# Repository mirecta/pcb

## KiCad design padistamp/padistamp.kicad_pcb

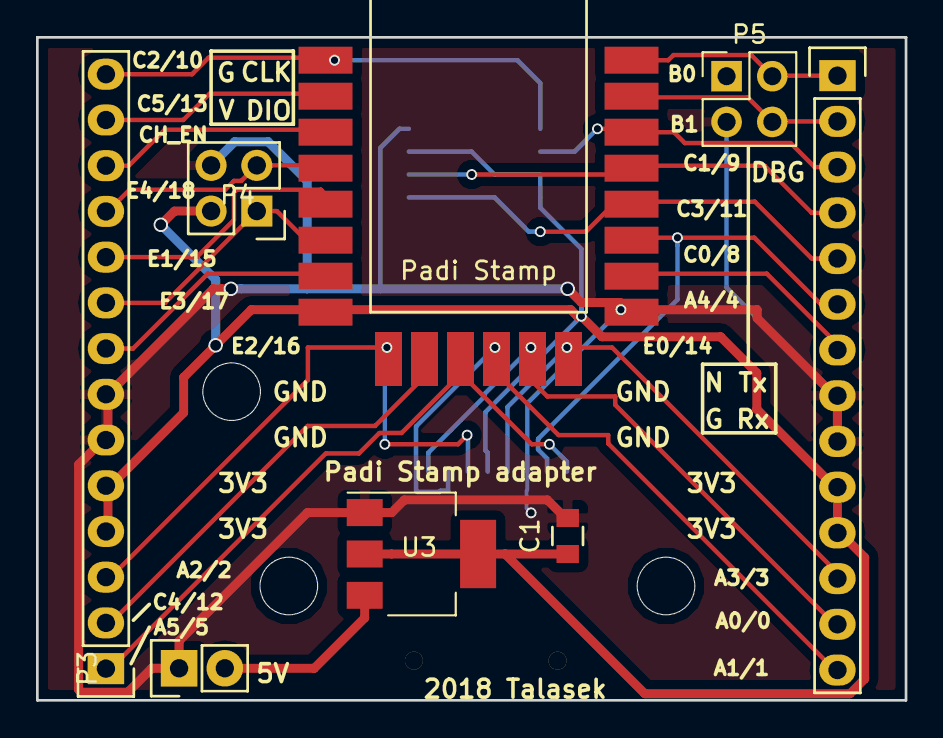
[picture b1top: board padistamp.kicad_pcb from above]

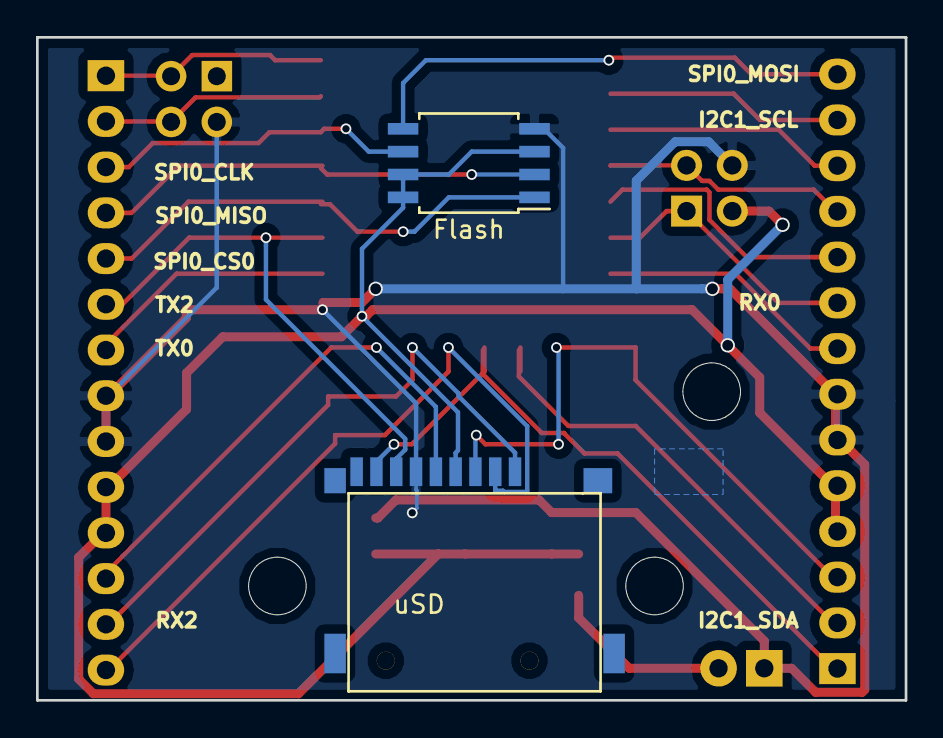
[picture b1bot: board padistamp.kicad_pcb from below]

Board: 2 copper layers, 48.3 x 36.8 mm, 10 parts (2 on the bottom side), 23 nets.

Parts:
C1: 0.1u; C_0805
Flash: 25LC_EEPROM; SOIJ-8_5.3x5.3mm_Pitch1.27mm
P1, P2: CONN_01X14; Pin_Header_Straight_1x14
P3: 5V; Pin_Header_Straight_1x02
P4: SWD; Pin_Header_Straight_2x02
P5: Conn_02x02_Odd_Even; Pin_Header_Straight_2x02_Pitch2.54mm
Padi Stamp: padi_stamp
U3: TLV1117; SOT-223
uSD: uSD

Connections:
unnamed: C1.1, Flash.3, Flash.7, Flash.8, P1.4, P1.5, P2.10, P2.11, P4.2, Padi Stamp.8, U3.2, U3.4, uSD.4
unnamed: C1.2, Flash.4, P1.6, P1.7, P2.8, P2.9, P3.1, P4.4, P5.3, Padi Stamp.15, U3.1, uSD.6
unnamed: P1.1, Padi Stamp.11, uSD.8
unnamed: P1.2, Padi Stamp.10
unnamed: P1.3, Padi Stamp.9, uSD.3
unnamed: P1.8, Padi Stamp.7
unnamed: P1.9, P4.1, Padi Stamp.6
unnamed: P1.10, Padi Stamp.5
unnamed: P1.11, P4.3, Padi Stamp.4
unnamed: P1.12, Padi Stamp.3
unnamed: P1.13, Padi Stamp.2
unnamed: Flash.5, P1.14, Padi Stamp.1
unnamed: P2.1, P5.2, Padi Stamp.22
unnamed: P2.2, P5.4, Padi Stamp.21
unnamed: Flash.6, P2.3, Padi Stamp.20
unnamed: Flash.2, P2.4, Padi Stamp.19
unnamed: Flash.1, P2.5, Padi Stamp.18
unnamed: P2.6, Padi Stamp.17, uSD.7
unnamed: P2.7, Padi Stamp.16
unnamed: P2.12, Padi Stamp.14, uSD.5
unnamed: P2.13, Padi Stamp.13, uSD.1
unnamed: P2.14, Padi Stamp.12, uSD.2
unnamed: P3.2, U3.3

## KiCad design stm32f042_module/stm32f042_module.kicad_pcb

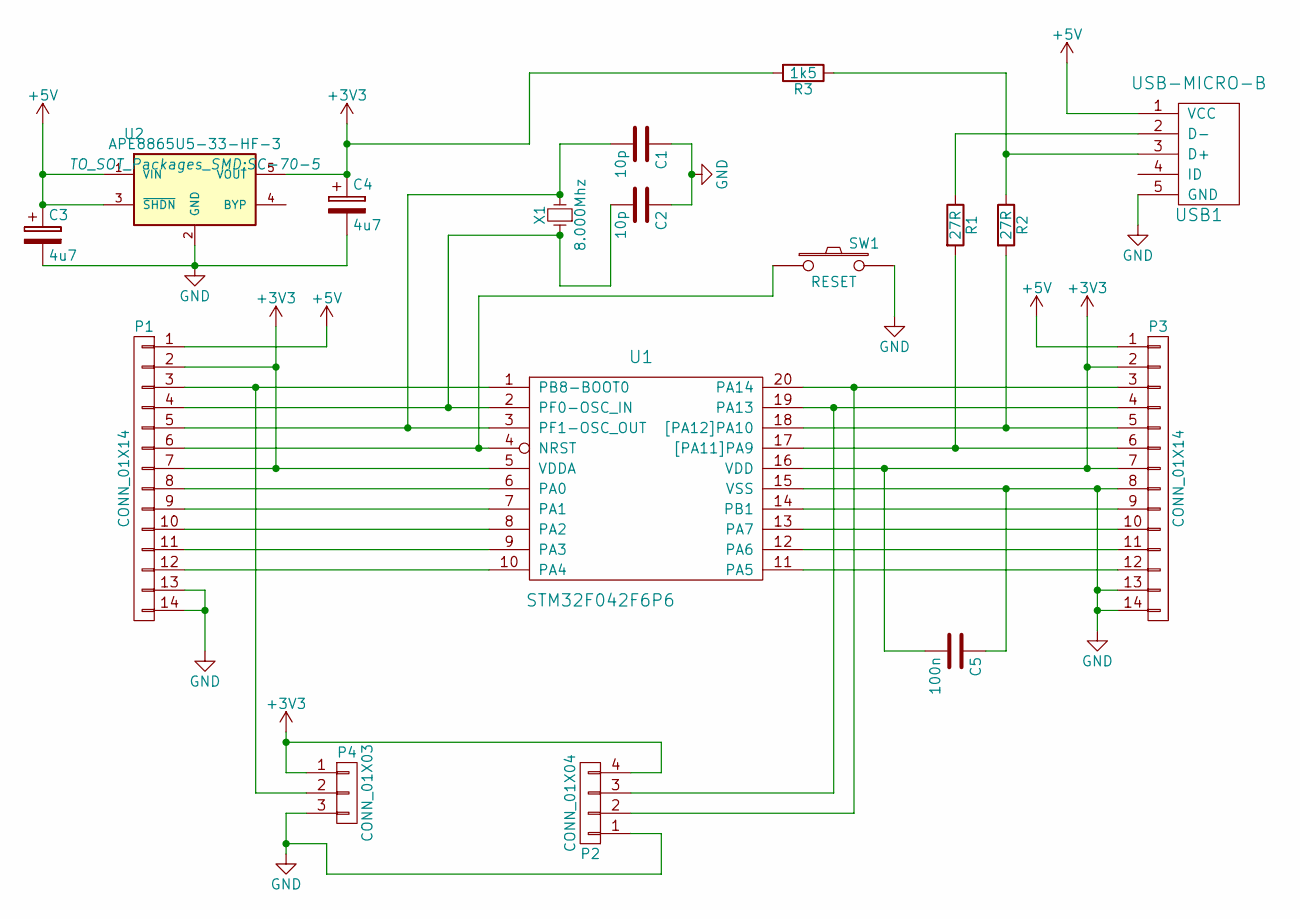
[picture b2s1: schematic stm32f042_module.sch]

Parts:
C1, C2: 10p; C_0603_HandSoldering
C3, C4: 4u7; C_0603_HandSoldering
C5: 100n; C_0603_HandSoldering
P1, P3: CONN_01X14; Pin_Header_Straight_1x14
P2: CONN_01X04; Pin_Header_Straight_1x04
P4: CONN_01X03; Pin_Header_Straight_1x03
R1, R2: 27R; R_0603_HandSoldering
R3: 1k5; R_0603_HandSoldering
SW1: RESET; MICROSWITCH-3x6
U1: STM32F042F6P6; TSSOP-20_4.4x6.5mm_Pitch0.65mm
U2: APE8865U5-33-HF-3; SC-70-5
USB1: USB-MICRO-B; USB-MICRO-B-SMT
X1: 8.000Mhz; SMT_5032

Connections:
+3V3: C4.1, C5.2, P1.2, P1.7, P2.4, P3.2, P3.7, P4.1, R3.2, U1.5 (VDDA), U1.16 (VDD), U2.5 (VOUT)
+5V: C3.1, P1.1, P3.1, U2.1 (VIN), U2.3 (~SHDN~), USB1.1 (VCC)
GND: C1.1, C2.1, C3.2, C4.2, C5.1, P1.13, P1.14, P2.1, P3.8, P3.13, P3.14, P4.3, SW1.2, U1.15 (VSS), U2.2 (GND), USB1.5 (GND); also elsewhere on the board
unnamed: C1.2, P1.5, U1.3 (PF1-OSC_OUT), X1.2
unnamed: C2.2, P1.4, U1.2 (PF0-OSC_IN), X1.1
unnamed: P1.3, P4.2, U1.1 (PB8-BOOT0)
unnamed 6: P1.6, SW1.1, U1.4 (NRST); also elsewhere on the board
unnamed: P1.8, U1.6 (PA0)
unnamed: P1.9, U1.7 (PA1)
unnamed: P1.10, U1.8 (PA2)
unnamed: P1.11, U1.9 (PA3)
unnamed: P1.12, U1.10 (PA4)
unnamed: P2.2, P3.3, U1.20 (PA14)
unnamed: P2.3, P3.4, U1.19 (PA13)
unnamed: P3.5, R2.2, U1.18 ([PA12]PA10)
unnamed: P3.6, R1.2, U1.17 ([PA11]PA9)
unnamed: P3.9, U1.14 (PB1)
unnamed: P3.10, U1.13 (PA7)
unnamed: P3.11, U1.12 (PA6)
unnamed: P3.12, U1.11 (PA5)
unnamed: R1.1, USB1.2 (D-)
unnamed: R2.1, R3.1, USB1.3 (D+)

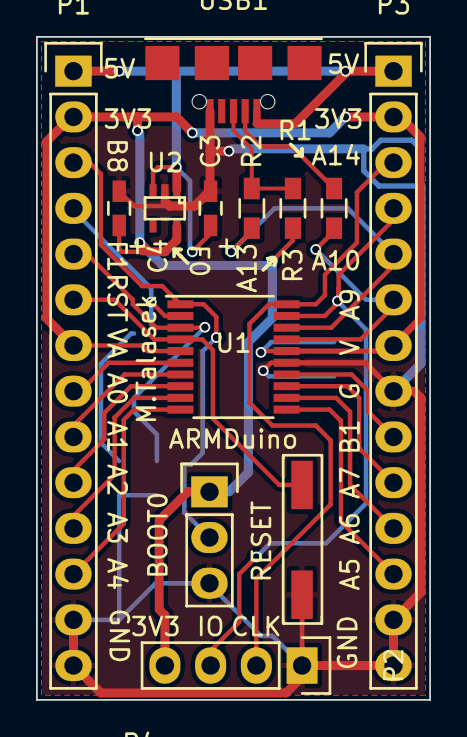
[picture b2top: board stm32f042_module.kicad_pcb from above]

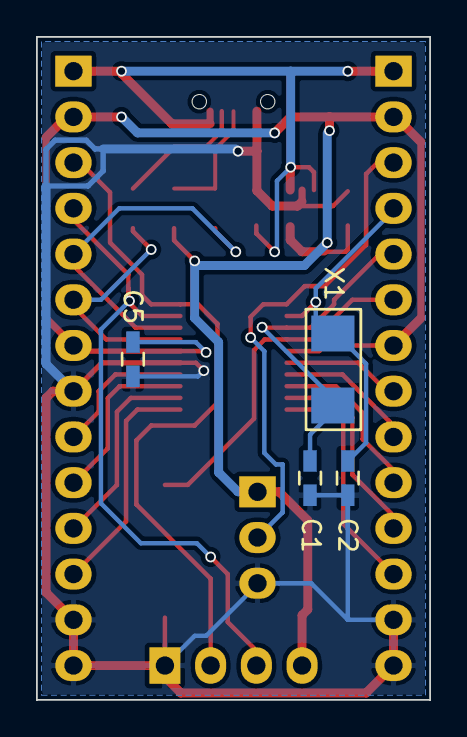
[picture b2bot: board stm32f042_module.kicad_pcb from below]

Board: 2 copper layers, 21.8 x 36.8 mm, 17 parts (4 on the bottom side), 22 nets.

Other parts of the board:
RESET: RESET; MICROSWITCH-3x6

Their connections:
GND: RESET.2; also elsewhere on the board
unnamed 6: RESET.1; also elsewhere on the board

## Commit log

2014-09-16 add project decoder
2016-03-08 add project
2016-03-10 add usb conn and footprint
2016-03-10 fix usb conn
2016-03-11 start design pcb
2016-03-12 final board
2017-07-25 add sdcard footprint
2017-07-26 add footprint padi stamp
2017-07-26 final
2017-10-29 add stabiliser and swd pins
2017-10-30 add new gerber
2018-02-13 not yet done , add serial conn , serial eeprom
2018-02-13 filan
2018-02-27 add spaces where need it
2018-03-02 V3 board
